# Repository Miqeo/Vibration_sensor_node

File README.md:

# Vibration sensor node

## Motivation

Since my first endeavour into PCB and CAD design, I have always wanted to create something from start to finish. This was possible with one of the previous projects I was a part of, where there was a need to make a Raspberry Pi HAT, the software to run with it, and the corresponding casing.

As that project came to a close, I wanted to make use of my time and extend my knowledge with this initiative to make something useful and to test the capabilities of FOSS software such as Freecad and Kicad.

This culminated in the amalgamation of sensors, storage, comms, and compute that can be called a “node” for the distributed sensor system.

As this is a work in progress, and the exact use might change with time, I do not want to point towards the problem it might, in the future, solve. The time-synchronised system of this kind may be used in places where other, physically connected or remote nodes are used now.

## Future capabilities

The planned capabilities of the node are to autonomously save vibration data and synchronize it in time with other nodes using a wireless link. The nodes equipped with the 3-axis gyroscope would also be able to track changes in rotation. 

## System elements

The system makes use of the small cyllindrical battery, repurposed from an ellectrical cigarette. The main computation is done by the STM32 microcontroller, which has access to the onboard accrellerometer-gyroscope combo and an extensible accelerometer via a board-to-board connector. The microcontroller is connected to the outside world via the wireless module and usb 2.0 via USB-C, which also acts as the charger for the unit. The data collected can be stored on the external SD card or the soldered-on QSPI flash.

[Here is the schematic document of the controller board](/pcb/accel_controller_schematic.pdf)

*Data flow of the system*

## Fabrication

*The main controller PCB*

*A sensor sub-board connected via a board-to-board connector*

*Model of the the sensor casing*

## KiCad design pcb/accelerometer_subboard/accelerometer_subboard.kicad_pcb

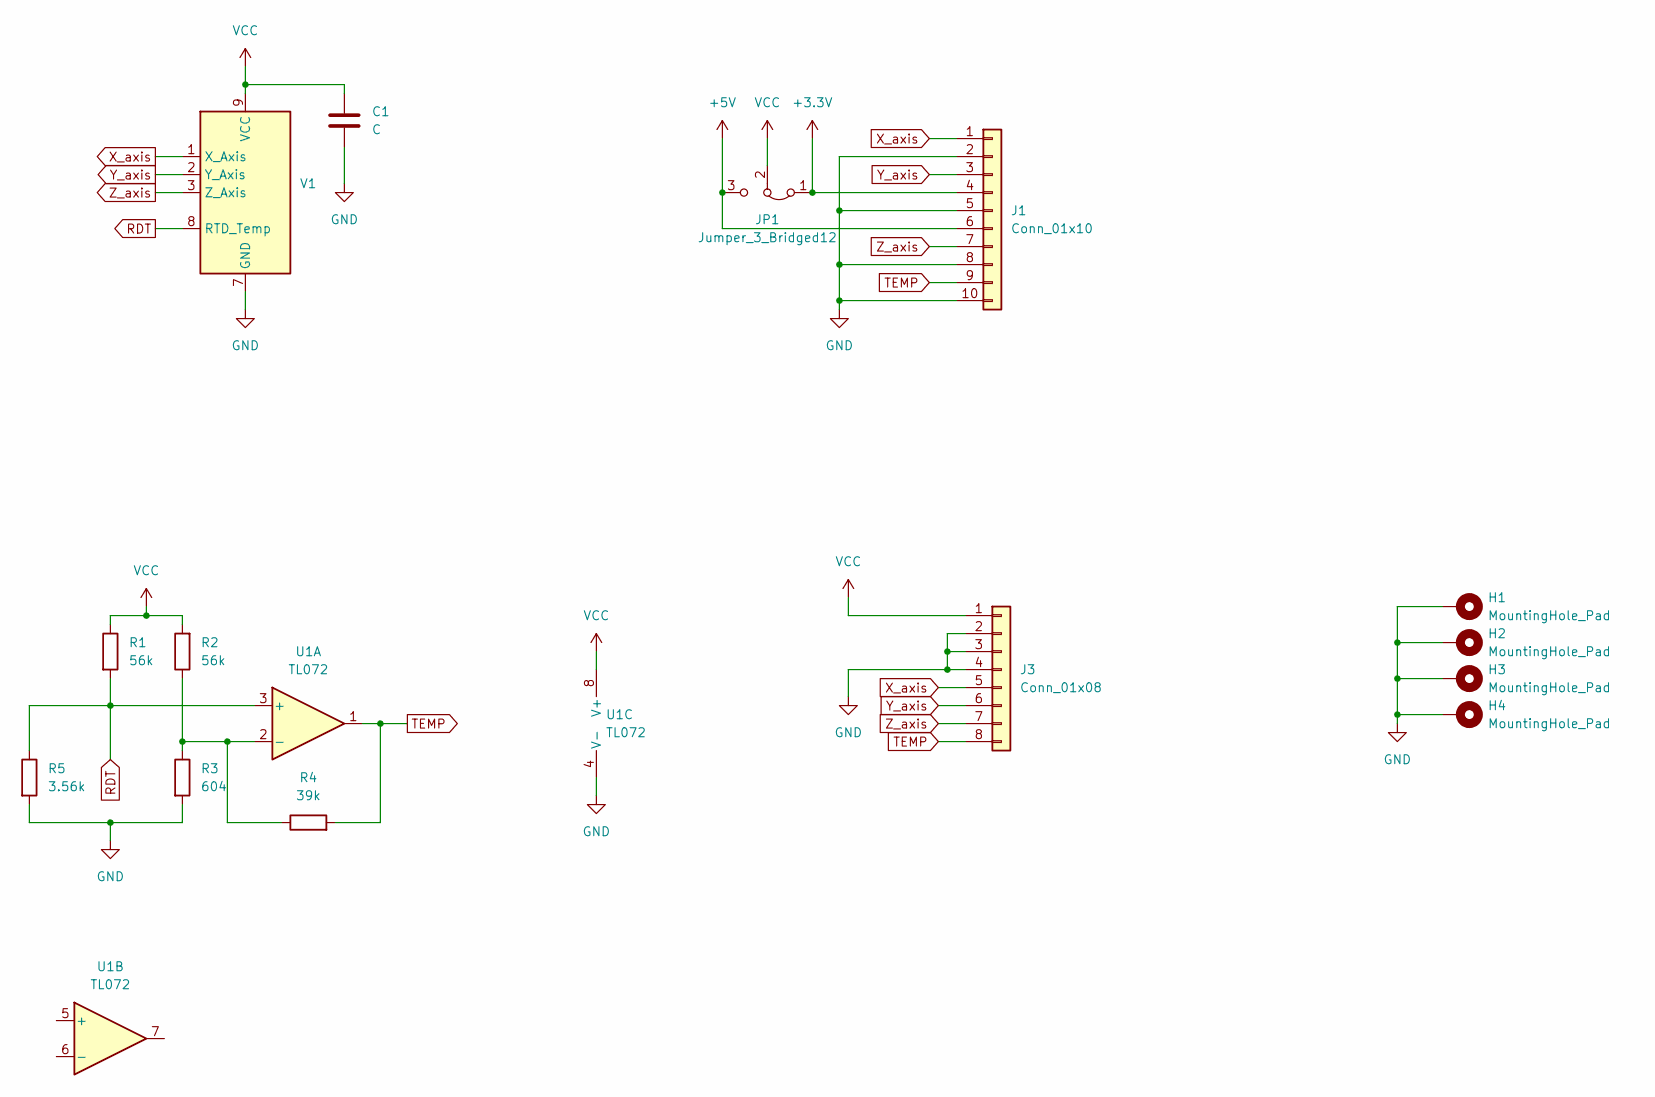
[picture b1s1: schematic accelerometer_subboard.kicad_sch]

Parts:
C1: C; C_0805_2012Metric
H1, H2, H3, H4: MountingHole_Pad; MountingHole_2.7mm_M2.5_DIN965_Pad
J1: Conn_01x10; AMPHENOL_10132798-011100LF
J3: Conn_01x08; PinHeader_2x04_P2.54mm_Vertical
JP1: Jumper_3_Bridged12; SolderJumper-3_P1.3mm_Bridged2Bar12_RoundedPad1.0x1.5mm
R1, R2: 56k; R_0805_2012Metric
R3: 604; R_0805_2012Metric
R4: 39k; R_0805_2012Metric
R5: 3.56k; R_0805_2012Metric
U1: TL072; TSSOP-8_4.4x3mm_P0.65mm
V1: TE_Connectivity_830M1

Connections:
+3.3V: J1.4, JP1.1 (A)
+5V: J1.6, JP1.3 (B)
GND: C1.2, H1.1, H2.1, H3.1, H4.1, J1.2, J1.5, J1.8, J1.10, J3.2, J3.3, J3.4, R3.2, R5.2, U1.4 (V-), V1.7 (GND)
unnamed: R2.1, R3.1, R4.1, U1.2 (-)
RDT: R1.2, R5.1, U1.3 (+), V1.8 (RTD_Temp)
TEMP: J1.9, J3.8, R4.2, U1.1
VCC: C1.1, J3.1, JP1.2 (C), R1.1, R2.2, U1.8 (V+), V1.9 (VCC)
X_axis: J1.1, J3.5, V1.1 (X_Axis)
Y_axis: J1.3, J3.6, V1.2 (Y_Axis)
Z_axis: J1.7, J3.7, V1.3 (Z_Axis)

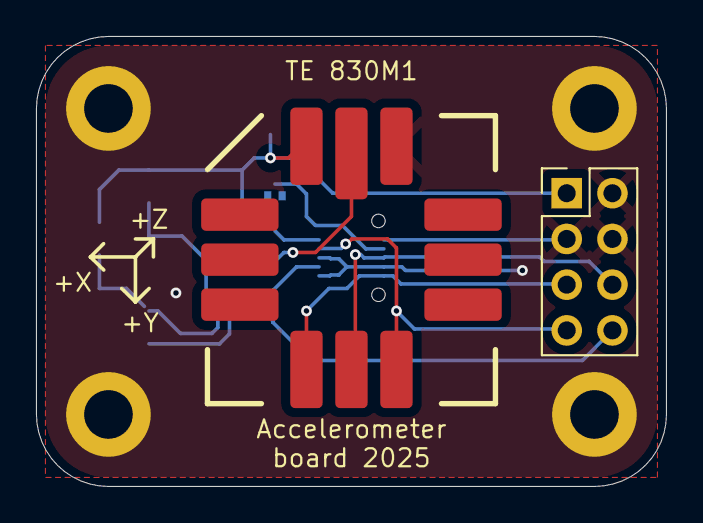
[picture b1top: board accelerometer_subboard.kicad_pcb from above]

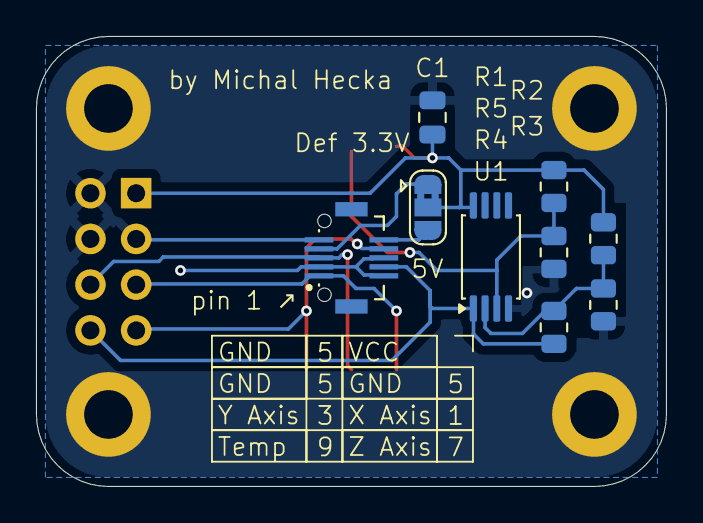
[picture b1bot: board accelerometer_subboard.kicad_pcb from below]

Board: 2 copper layers, 35.0 x 25.0 mm, 15 parts (9 on the bottom side), 10 nets.

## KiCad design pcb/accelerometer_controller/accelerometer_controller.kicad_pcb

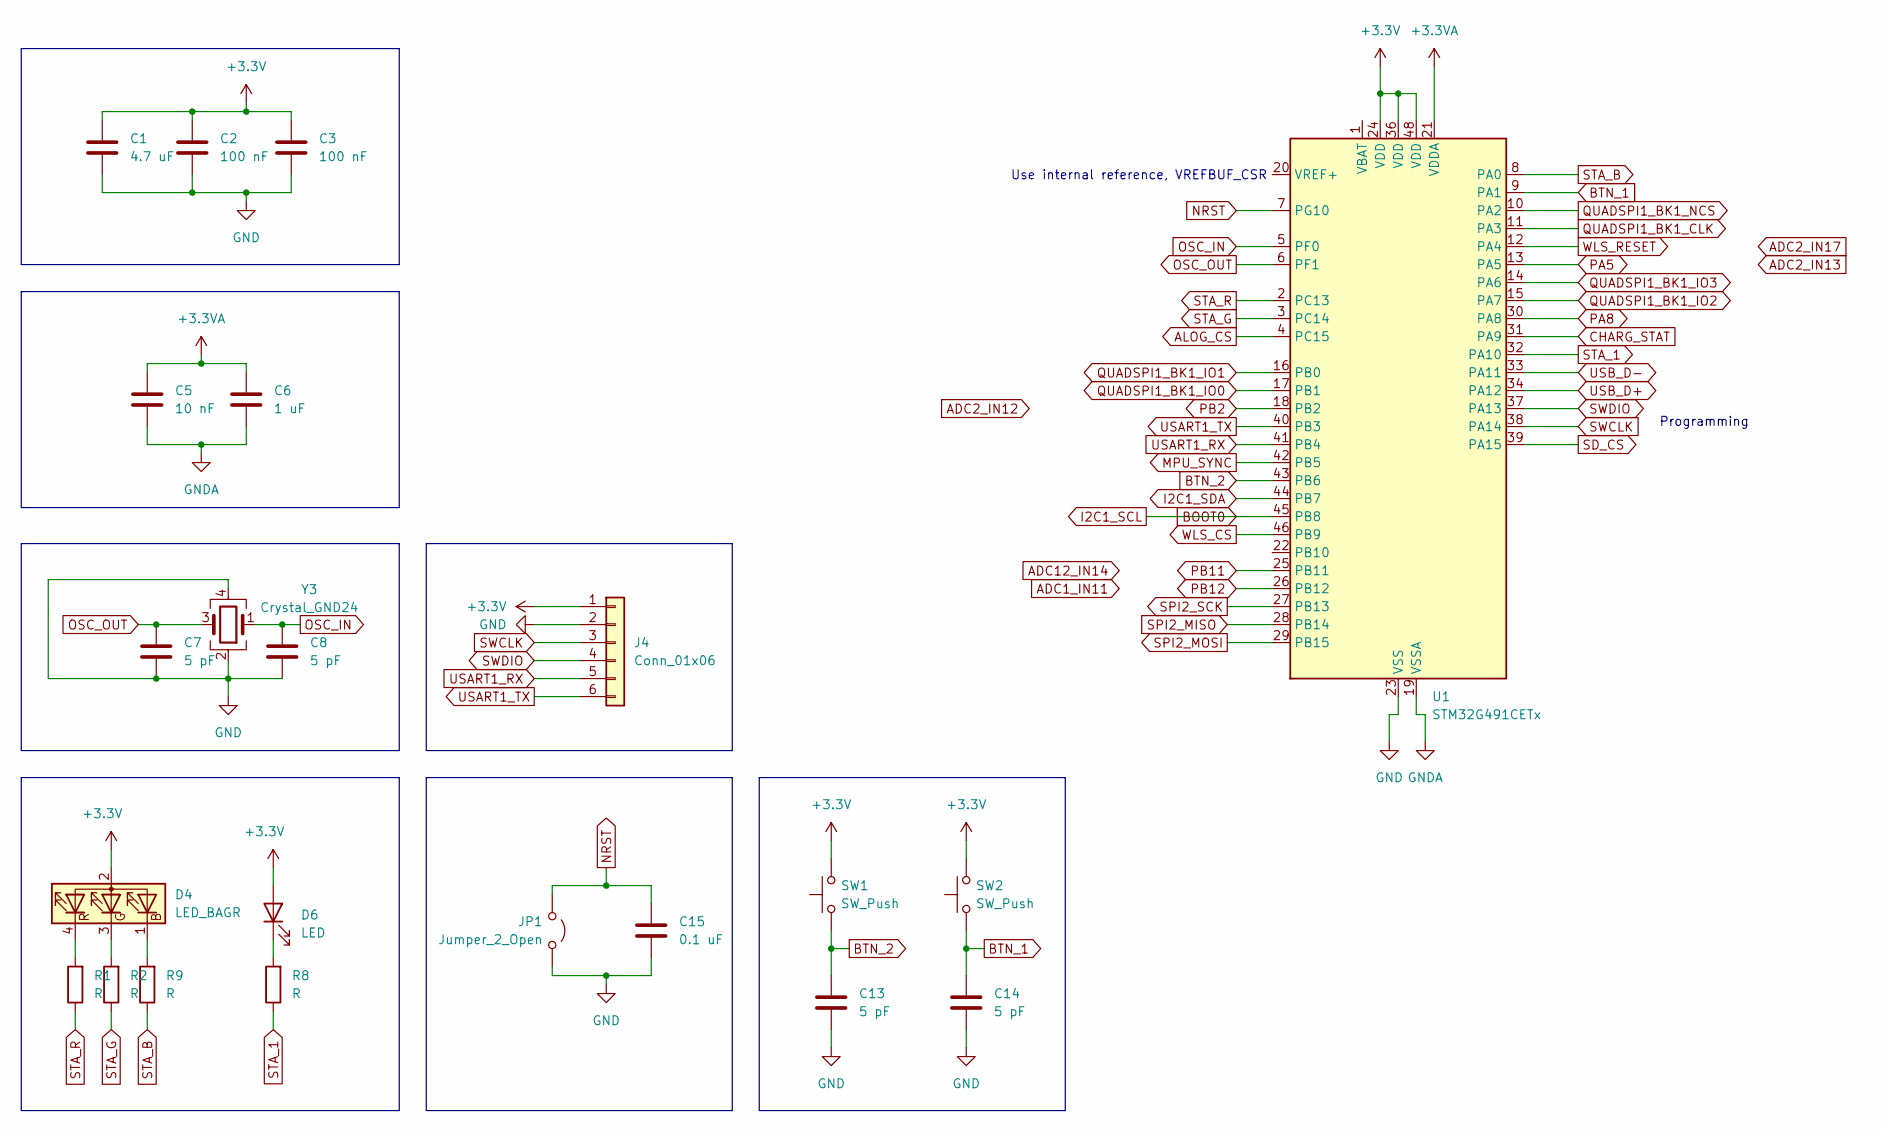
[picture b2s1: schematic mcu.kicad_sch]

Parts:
C1: 4.7 uF; C_0805_2012Metric
C2, C3: 100 nF; C_0805_2012Metric
C5: 10 nF; C_0805_2012Metric
C6: 1 uF; C_0805_2012Metric
C7, C8, C13, C14: 5 pF; C_0805_2012Metric
C15: 0.1 uF; C_0805_2012Metric
D4: LED_BAGR; OSTB0805C1E-A-0.8T
D6: LED; LED_0805_2012Metric
J4: Conn_01x06; PinHeader_2x03_P2.54mm_Vertical
JP1: Jumper_2_Open; SolderJumper-2_P1.3mm_Open_RoundedPad1.0x1.5mm
R1, R2, R8, R9: R; R_0805_2012Metric
SW1, SW2: SW_Push; SW_Push_1P1T_XKB_TS-1187A
U1: STM32G491CETx; LQFP-48_7x7mm_P0.5mm
Y3: Crystal_GND24; Crystal_SMD_3225-4Pin_3.2x2.5mm

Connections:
+3.3V: C1.1, C2.1, C3.1, C5.1, C6.1, D4.2 (A), D6.2 (A), J4.1, SW1.2, SW2.2, U1.21 (VDDA), U1.24 (VDD), U1.36 (VDD), U1.48 (VDD); also elsewhere on the board
ALOG_CS: U1.4 (PC15); also elsewhere on the board
BOOT0: U1.45 (PB8); also elsewhere on the board
BTN_1: C14.1, SW2.1, U1.9 (PA1)
BTN_2: C13.1, SW1.1, U1.43 (PB6)
CHARG_STAT: U1.31 (PA9); also elsewhere on the board
GND: C1.2, C2.2, C3.2, C5.2, C6.2, C7.2, C8.2, C13.2, C14.2, C15.2, J4.2, JP1.1 (A), U1.19 (VSSA), U1.23 (VSS), U1.35 (VSS), U1.47 (VSS), Y3.2, Y3.4; also elsewhere on the board
I2C1_SDA: U1.44 (PB7); also elsewhere on the board
MPU_SYNC: U1.42 (PB5); also elsewhere on the board
NRST: C15.1, JP1.2 (B), U1.7 (PG10)
unnamed: D4.1 (BK), R9.2
unnamed: D4.3 (GK), R2.2
unnamed: D4.4 (RK), R1.2
unnamed: D6.1 (K), R8.2
OSC_IN: C8.1, U1.5 (PF0), Y3.1
OSC_OUT: C7.1, U1.6 (PF1), Y3.3
PA5: U1.13 (PA5); also elsewhere on the board
PA8: U1.30 (PA8); also elsewhere on the board
PB2: U1.18 (PB2); also elsewhere on the board
PB11: U1.25 (PB11); also elsewhere on the board
PB12: U1.26 (PB12); also elsewhere on the board
QUADSPI1_BK1_CLK: U1.11 (PA3); also elsewhere on the board
QUADSPI1_BK1_IO0: U1.17 (PB1); also elsewhere on the board
QUADSPI1_BK1_IO1: U1.16 (PB0); also elsewhere on the board
QUADSPI1_BK1_IO2: U1.15 (PA7); also elsewhere on the board
QUADSPI1_BK1_IO3: U1.14 (PA6); also elsewhere on the board
QUADSPI1_BK1_NCS: U1.10 (PA2); also elsewhere on the board
SD_CS: U1.39 (PA15); also elsewhere on the board
SPI2_MISO: U1.28 (PB14); also elsewhere on the board
SPI2_MOSI: U1.29 (PB15); also elsewhere on the board
SPI2_SCK: U1.27 (PB13); also elsewhere on the board
STA_1: R8.1, U1.32 (PA10)
STA_B: R9.1, U1.8 (PA0)
STA_G: R2.1, U1.3 (PC14)
STA_R: R1.1, U1.2 (PC13)
SWCLK: J4.3, U1.38 (PA14)
SWDIO: J4.4, U1.37 (PA13)
USART1_RX: J4.5, U1.41 (PB4)
USART1_TX: J4.6, U1.40 (PB3)
USB_D+: U1.34 (PA12); also elsewhere on the board
USB_D-: U1.33 (PA11); also elsewhere on the board
WLS_CS: U1.46 (PB9); also elsewhere on the board
WLS_RESET: U1.12 (PA4); also elsewhere on the board

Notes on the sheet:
Use internal reference, VREFBUF_CSR
Programming

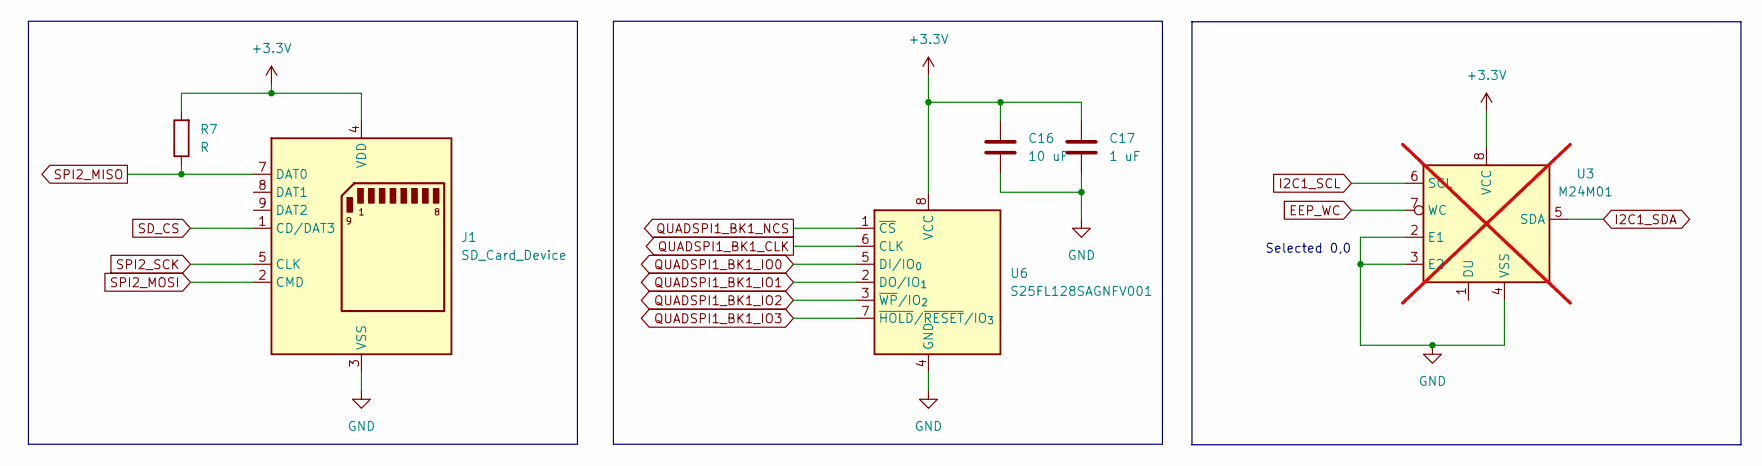
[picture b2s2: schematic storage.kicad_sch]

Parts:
C16: 10 uF; C_1206_3216Metric
C17: 1 uF; C_0805_2012Metric
J1: SD_Card_Device; 112J-TDAR-R01_ATT
R7: R; R_0805_2012Metric
U3: M24M01; SOIC-8_5.3x5.3mm_P1.27mm; not fitted
U6: S25FL128SAGNFV001; WSON-8-1EP_6x5mm_P1.27mm_EP3.4x4.3mm

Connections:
+3.3V: C16.1, C17.1, J1.4 (VDD), R7.2, U3.8 (VCC), U6.8 (VCC); also elsewhere on the board
GND: C16.2, C17.2, J1.3 (VSS), J1.6 (VSS), J1.12, J1.14, J1.15, U3.2 (E1), U3.3 (E2), U3.4 (VSS), U6.4 (GND); also elsewhere on the board
QUADSPI1_BK1_CLK: U6.6 (CLK); also elsewhere on the board
QUADSPI1_BK1_IO0: U6.5 (DI/IO_{0}); also elsewhere on the board
QUADSPI1_BK1_IO1: U6.2 (DO/IO_{1}); also elsewhere on the board
QUADSPI1_BK1_IO2: U6.3 (~WP/IO_{2}); also elsewhere on the board
QUADSPI1_BK1_IO3: U6.7 (~HOLD/~RESET/IO_{3}); also elsewhere on the board
QUADSPI1_BK1_NCS: U6.1 (~CS); also elsewhere on the board
SD_CS: J1.1 (CD/DAT3); also elsewhere on the board
SPI2_MISO: J1.7 (DAT0), R7.1; also elsewhere on the board
SPI2_MOSI: J1.2 (CMD); also elsewhere on the board
SPI2_SCK: J1.5 (CLK); also elsewhere on the board

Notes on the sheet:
Selected 0,0

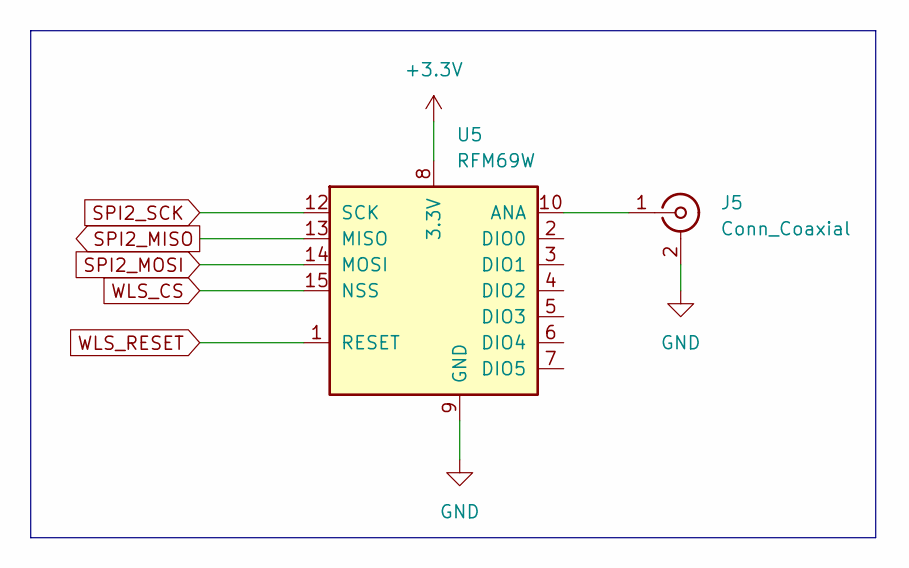
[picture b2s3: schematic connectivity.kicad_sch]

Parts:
J5: Conn_Coaxial; ADAMTECH_RF2-143-T-17-50-G
U5: RFM69W; HOPERF_RFM69HW

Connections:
+3.3V: U5.8 (3.3V); also elsewhere on the board
GND: J5.2 (Ext), U5.9 (GND), U5.11 (GND); also elsewhere on the board
unnamed: J5.1 (In), U5.10 (ANA)
SPI2_MISO: U5.13 (MISO); also elsewhere on the board
SPI2_MOSI: U5.14 (MOSI); also elsewhere on the board
SPI2_SCK: U5.12 (SCK); also elsewhere on the board
WLS_CS: U5.15 (NSS); also elsewhere on the board
WLS_RESET: U5.1 (RESET); also elsewhere on the board

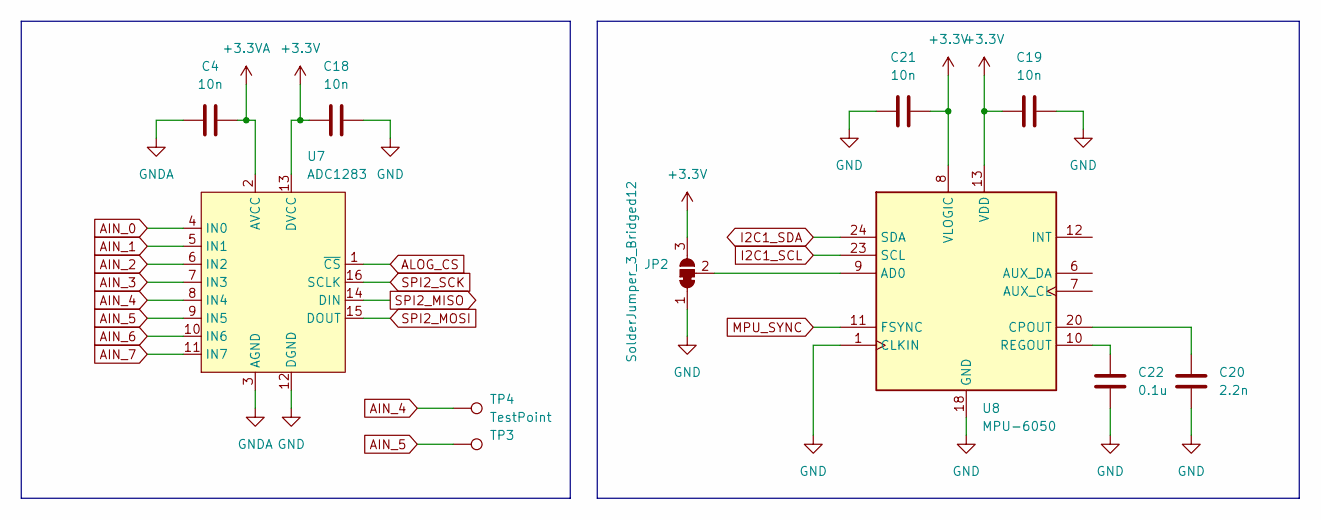
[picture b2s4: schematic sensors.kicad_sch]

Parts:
C4, C18, C19, C21: 10n; C_0805_2012Metric
C20: 2.2n; C_0805_2012Metric
C22: 0.1u; C_0805_2012Metric
JP2: SolderJumper_3_Bridged12; SolderJumper-3_P1.3mm_Bridged12_RoundedPad1.0x1.5mm
TP3, TP4: TestPoint; TestPoint_Pad_D1.0mm
U7: ADC1283; TSSOP-16_4.4x5mm_P0.65mm
U8: MPU-6050; InvenSense_QFN-24_4x4mm_P0.5mm

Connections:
+3.3V: C4.2, C18.1, C19.1, C21.2, JP2.3 (B), U7.2 (AVCC), U7.13 (DVCC), U8.8 (VLOGIC), U8.13 (VDD); also elsewhere on the board
AIN_0: U7.4 (IN0); also elsewhere on the board
AIN_1: U7.5 (IN1); also elsewhere on the board
AIN_2: U7.6 (IN2); also elsewhere on the board
AIN_3: U7.7 (IN3); also elsewhere on the board
AIN_4: TP4.1, U7.8 (IN4)
AIN_5: TP3.1, U7.9 (IN5)
AIN_6: U7.10 (IN6)
AIN_7: U7.11 (IN7)
ALOG_CS: U7.1 (~CS); also elsewhere on the board
BOOT0: U8.23 (SCL); also elsewhere on the board
GND: C4.1, C18.2, C19.2, C20.2, C21.1, C22.2, JP2.1 (A), U7.3 (AGND), U7.12 (DGND), U8.1 (CLKIN), U8.18 (GND); also elsewhere on the board
I2C1_SDA: U8.24 (SDA); also elsewhere on the board
MPU_SYNC: U8.11 (FSYNC); also elsewhere on the board
unnamed: JP2.2 (C), U8.9 (AD0)
unnamed: C20.1, U8.20 (CPOUT)
unnamed: C22.1, U8.10 (REGOUT)
SPI2_MISO: U7.14 (DIN); also elsewhere on the board
SPI2_MOSI: U7.15 (DOUT); also elsewhere on the board
SPI2_SCK: U7.16 (SCLK); also elsewhere on the board

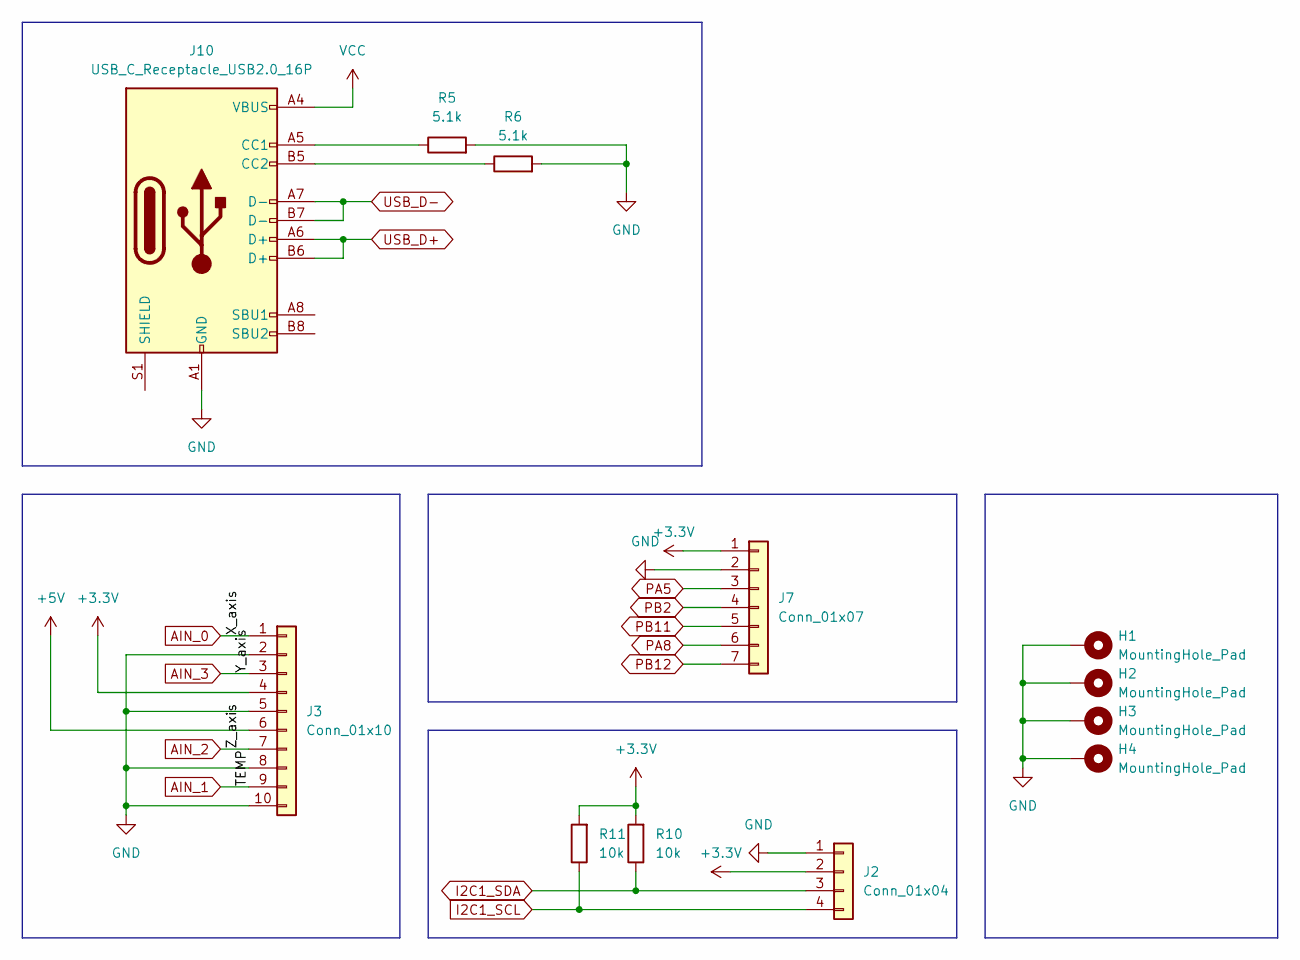
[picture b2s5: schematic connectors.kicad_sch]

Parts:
H1, H2, H3, H4: MountingHole_Pad; MountingHole_2.7mm_M2.5_DIN965_Pad
J2: Conn_01x04; JST_SH_SM04B-SRSS-TB_1x04-1MP_P1.00mm_Horizontal
J3: Conn_01x10; AMPHENOL_10132797-011100LF
J7: Conn_01x07; PinHeader_1x07_P2.54mm_Vertical
J10: USB_C_Receptacle_USB2.0_16P; USB_C_Receptacle_GCT_USB4105-xx-A_16P_TopMnt_Horizontal
R5, R6: 5.1k; R_0805_2012Metric
R10, R11: 10k; R_0805_2012Metric

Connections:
+3.3V: J2.2, J3.4, J7.1, R10.2, R11.2; also elsewhere on the board
+5V: J3.6
AIN_0: J3.1; also elsewhere on the board
AIN_1: J3.9; also elsewhere on the board
AIN_2: J3.7; also elsewhere on the board
AIN_3: J3.3; also elsewhere on the board
BOOT0: J2.4, R11.1; also elsewhere on the board
GND: H1.1, H2.1, H3.1, H4.1, J2.1, J3.2, J3.5, J3.8, J3.10, J3.SH1, J3.SH2, J7.2, J10.A1 (GND), J10.A12 (GND), J10.B1 (GND), J10.B12 (GND), R5.2, R6.2; also elsewhere on the board
I2C1_SDA: J2.3, R10.1; also elsewhere on the board
unnamed: J10.A5 (CC1), R5.1
unnamed: J10.B5 (CC2), R6.1
PA5: J7.3; also elsewhere on the board
PA8: J7.6; also elsewhere on the board
PB2: J7.4; also elsewhere on the board
PB11: J7.5; also elsewhere on the board
PB12: J7.7; also elsewhere on the board
USB_D+: J10.A6 (D+), J10.B6 (D+); also elsewhere on the board
USB_D-: J10.A7 (D-), J10.B7 (D-); also elsewhere on the board
VCC: J10.A4 (VBUS), J10.A9 (VBUS), J10.B4 (VBUS), J10.B9 (VBUS); also elsewhere on the board

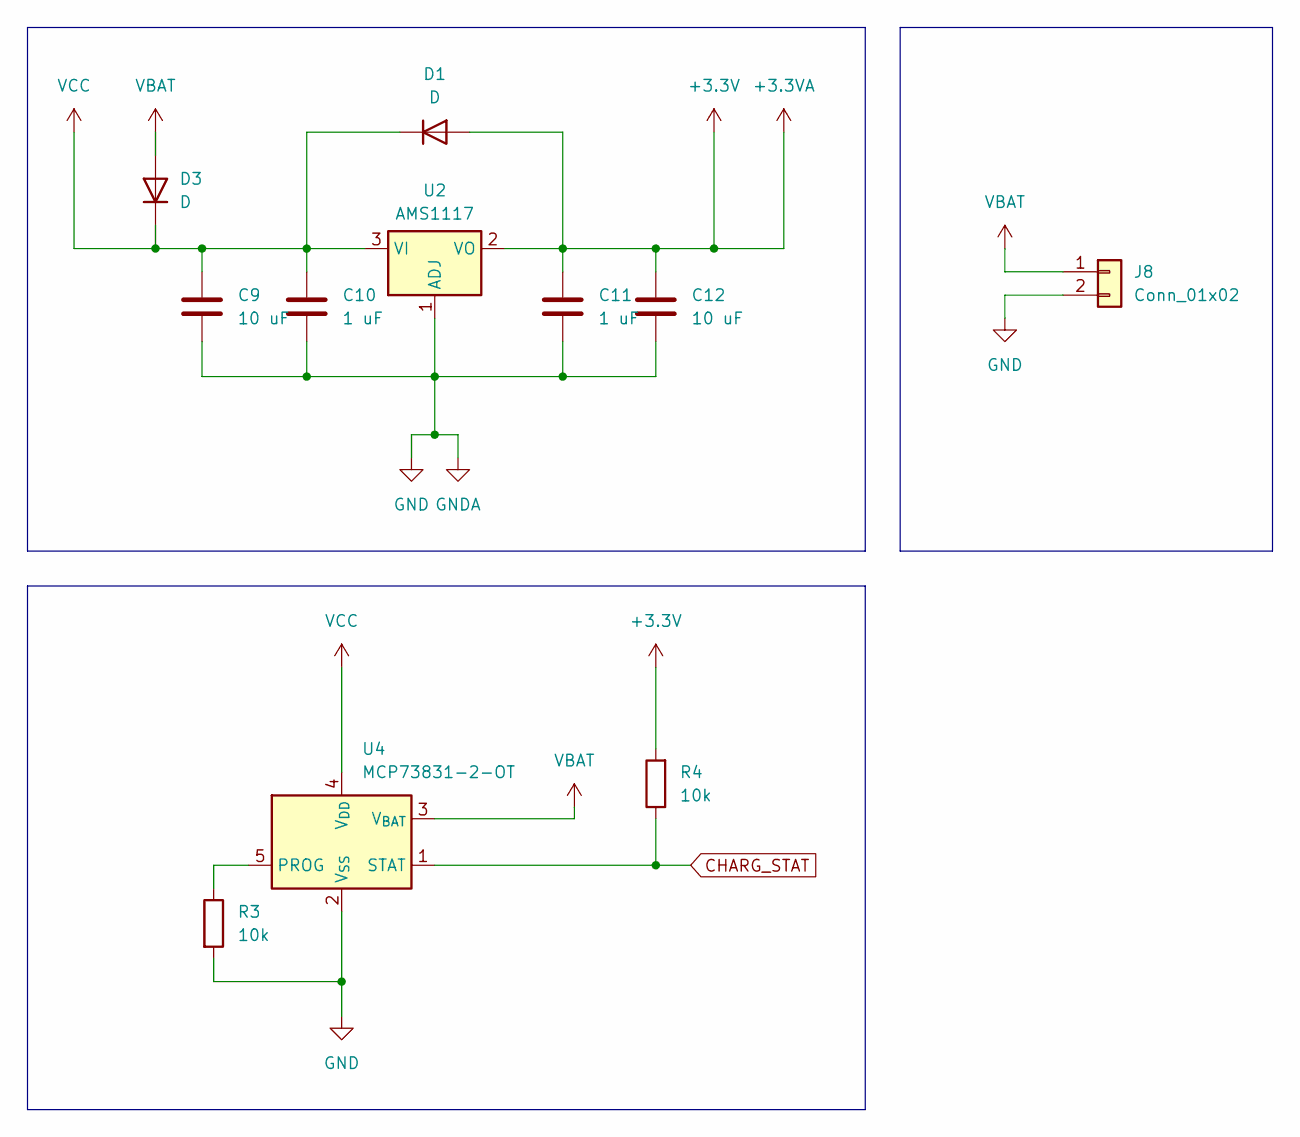
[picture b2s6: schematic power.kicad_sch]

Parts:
C9: 10 uF; CP_Radial_D4.0mm_P2.00mm
C10, C11: 1 uF; C_0805_2012Metric
C12: 10 uF; C_1206_3216Metric
D1, D3: D; D_SOD-123
J8: Conn_01x02; JST_PH_S2B-PH-SM4-TB_1x02-1MP_P2.00mm_Horizontal
R3, R4: 10k; R_0805_2012Metric
U2: AMS1117; SOT-89-3
U4: MCP73831-2-OT; SOT-23-5

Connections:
+3.3V: C11.1, C12.1, D1.2 (A), R4.2, U2.2 (VO); also elsewhere on the board
CHARG_STAT: R4.1, U4.1 (STAT); also elsewhere on the board
GND: C9.2, C10.2, C11.2, C12.2, J8.2, J8.MP, R3.2, U2.1 (ADJ), U4.2 (V_{SS}); also elsewhere on the board
unnamed: R3.1, U4.5 (PROG)
VBAT: D3.2 (A), J8.1, U4.3 (V_{BAT})
VCC: C9.1, C10.1, D1.1 (K), D3.1 (K), U2.3 (VI), U4.4 (V_{DD}); also elsewhere on the board

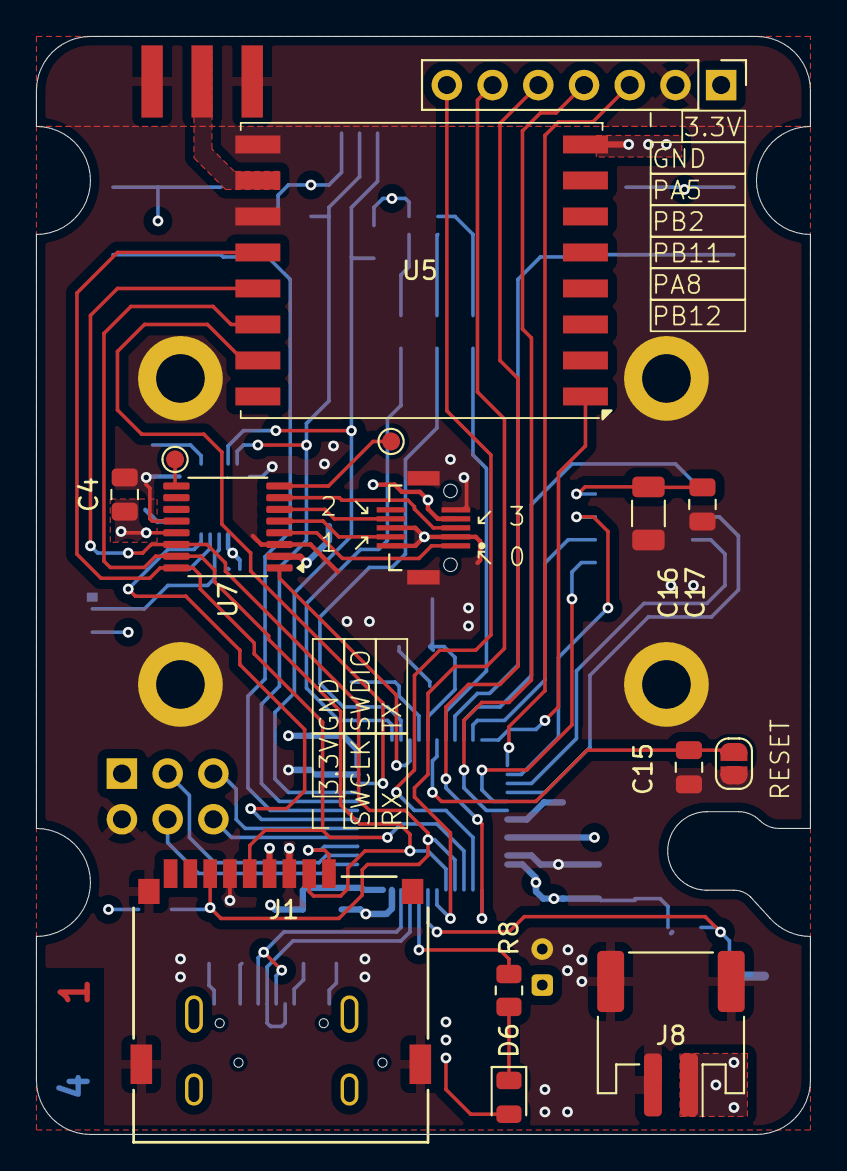
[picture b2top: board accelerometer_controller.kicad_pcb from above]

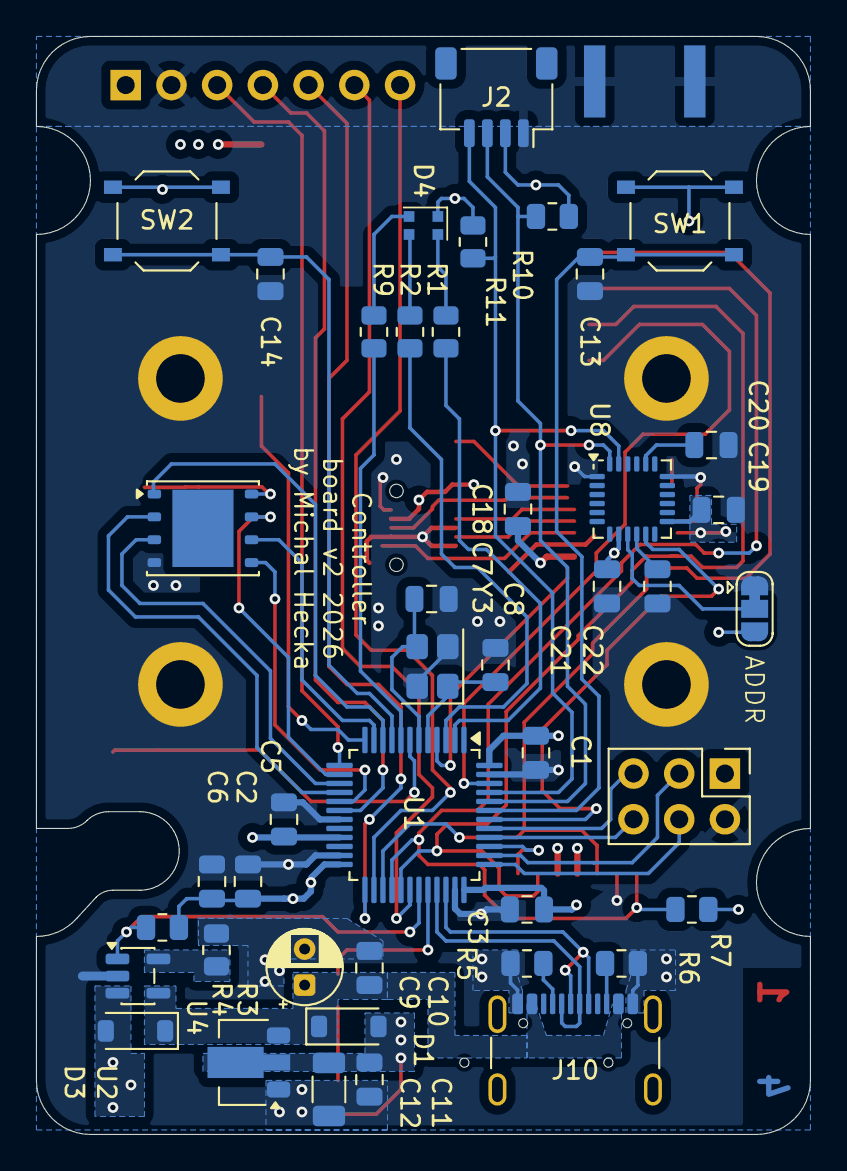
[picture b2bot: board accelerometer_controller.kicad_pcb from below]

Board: 4 copper layers, 43.0 x 61.0 mm, 63 parts (43 on the bottom side), 58 nets.
